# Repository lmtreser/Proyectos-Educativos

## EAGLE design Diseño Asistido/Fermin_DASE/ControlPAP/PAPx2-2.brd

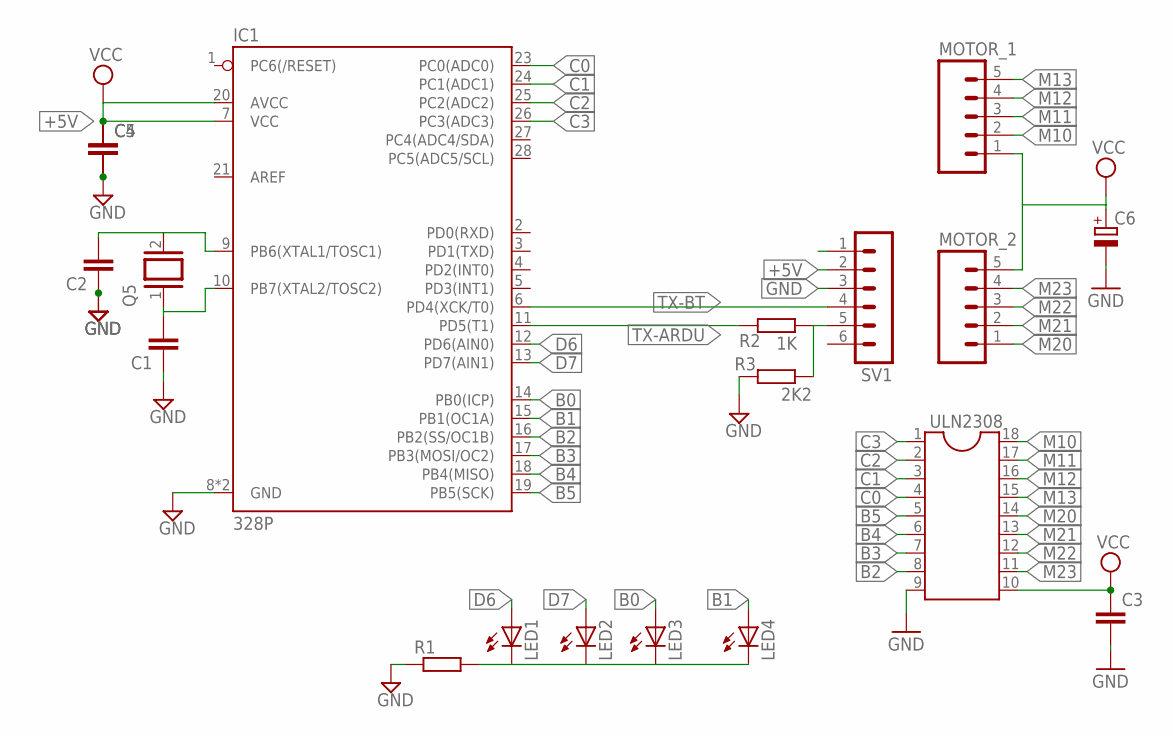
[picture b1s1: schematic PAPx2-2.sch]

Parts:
C1, C2: C-EU025-025X050; C025-025X050
C3, C4, C5: C-EU050-025X075; C050-025X075
C6: CPOL-EUE2.5-5; E2,5-5
IC1: 328P; DIP28
LED1, LED2, LED3, LED4: LED3MM; LED_3MM
MOTOR_1, MOTOR_2: M05; 05P
Q5: XTAL/S; QS
R1: R-EU_0207/7; 0207/7
R2: 1K; 0207/7
R3: 2K2; 0207/7
SV1: MA06-1
ULN2308: DIL18

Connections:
+5V: C4.1, C5.1, IC1.7 (VCC), IC1.20 (AVCC), SV1.2
B0: IC1.14 (PB0(ICP)), LED3.A
B1: IC1.15 (PB1(OC1A)), LED4.A
B2: IC1.16 (PB2(SS/OC1B)), ULN2308.8
B3: IC1.17 (PB3(MOSI/OC2)), ULN2308.7
B4: IC1.18 (PB4(MISO)), ULN2308.6
B5: IC1.19 (PB5(SCK)), ULN2308.5
C0: IC1.23 (PC0(ADC0)), ULN2308.4
C1: IC1.24 (PC1(ADC1)), ULN2308.3
C2: IC1.25 (PC2(ADC2)), ULN2308.2
C3: IC1.26 (PC3(ADC3)), ULN2308.1
D6: IC1.12 (PD6(AIN0)), LED1.A
D7: IC1.13 (PD7(AIN1)), LED2.A
GND: C1.1, C2.1, C3.2, C4.2, C5.2, C6.-, IC1.8 (GND), IC1.22 (GND), R1.1, R3.1, SV1.3, ULN2308.9
M10: MOTOR_1.2, ULN2308.18
M11: MOTOR_1.3, ULN2308.17
M12: MOTOR_1.4, ULN2308.16
M13: MOTOR_1.5, ULN2308.15
M20: MOTOR_2.1, ULN2308.14
M21: MOTOR_2.2, ULN2308.13
M22: MOTOR_2.3, ULN2308.12
M23: MOTOR_2.4, ULN2308.11
unnamed: R2.2, R3.2, SV1.5
unnamed: C1.2, IC1.10 (PB7(XTAL2/TOSC2)), Q5.1
unnamed: C2.2, IC1.9 (PB6(XTAL1/TOSC1)), Q5.2
unnamed: LED1.K (C), LED2.K (C), LED3.K (C), LED4.K (C), R1.2
TX-ARDU: IC1.11 (PD5(T1)), R2.1
TX-BT: IC1.6 (PD4(XCK/T0)), SV1.4
VCC: C3.1, C6.+, MOTOR_1.1, MOTOR_2.5, ULN2308.10

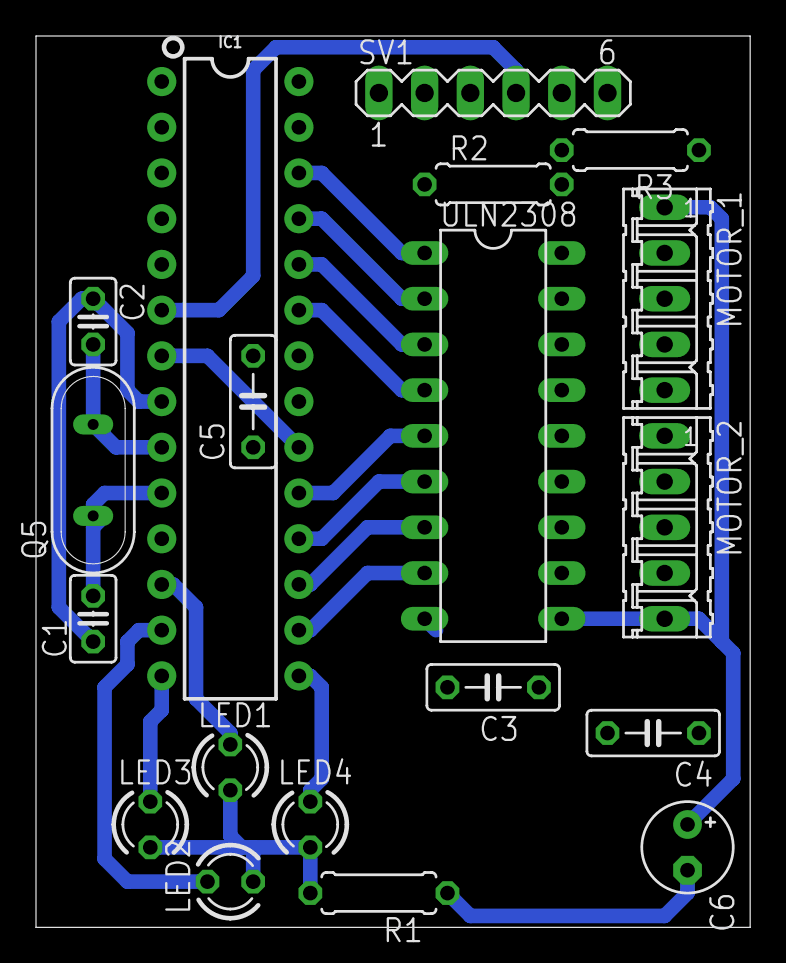
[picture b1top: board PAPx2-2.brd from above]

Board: 2 copper layers, 39.7 x 49.5 mm, 19 parts (0 on the bottom side), 29 nets.

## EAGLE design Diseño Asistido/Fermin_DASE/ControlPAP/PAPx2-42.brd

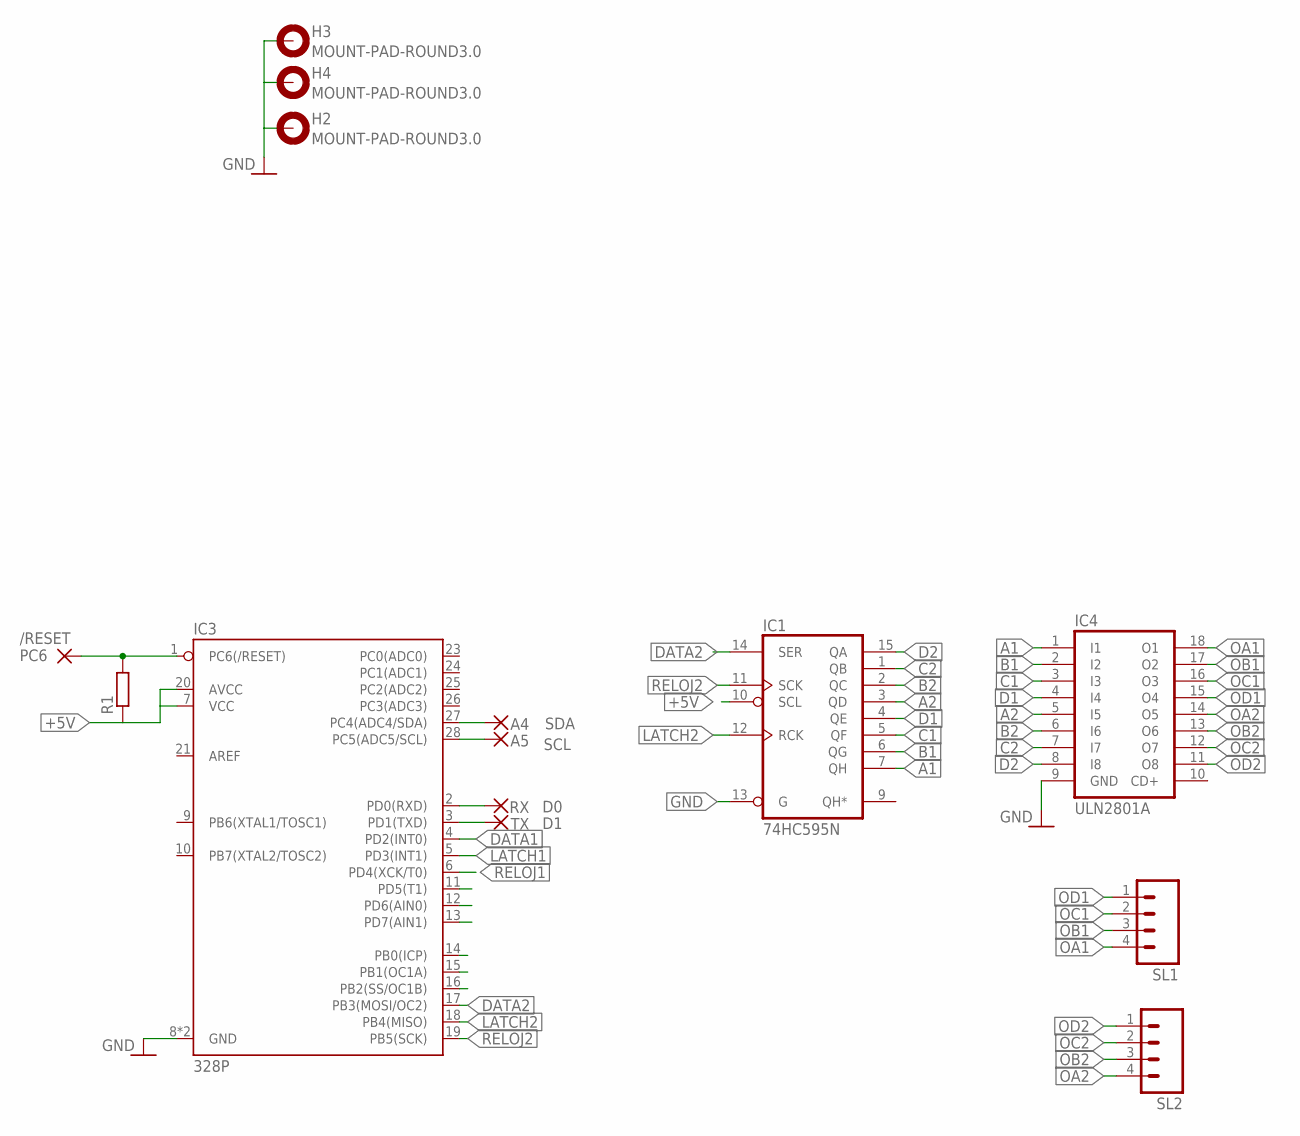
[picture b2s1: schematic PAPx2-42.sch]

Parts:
/RESET: PC6; 1,6/0,8
A4: SDA; 1,6/0,8
A5: SCL; 1,6/0,8
H2, H3, H4: MOUNT-PAD-ROUND3.0; 3,0-PAD
IC1: 74HC595N; DIL16
IC3: 328P; DIP28
IC4: ULN2801A; DIL18
R1: R-EU_0204/7; 0204/7
RX: D0; 1,6/0,8
SL1, SL2: M04; 04P
TX: D1; 1,6/0,8

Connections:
+5V: IC1.10 (SCL), IC3.7 (VCC), IC3.20 (AVCC), R1.1
A1: IC1.7 (QH), IC4.1 (I1)
A2: IC1.3 (QD), IC4.5 (I5)
B1: IC1.6 (QG), IC4.2 (I2)
B2: IC1.2 (QC), IC4.6 (I6)
C1: IC1.5 (QF), IC4.3 (I3)
C2: IC1.1 (QB), IC4.7 (I7)
D1: IC1.4 (QE), IC4.4 (I4)
D2: IC1.15 (QA), IC4.8 (I8)
DATA1: IC3.4 (PD2(INT0))
DATA2: IC1.14 (SER), IC3.17 (PB3(MOSI/OC2))
GND: H2.B3,0, H3.B3,0, H4.B3,0, IC1.8 (GND), IC1.13 (G), IC3.8 (GND), IC3.22 (GND), IC4.9 (GND)
LATCH1: IC3.5 (PD3(INT1))
LATCH2: IC1.12 (RCK), IC3.18 (PB4(MISO))
unnamed: IC3.2 (PD0(RXD)), RX.1
unnamed: IC3.3 (PD1(TXD)), TX.1
unnamed: /RESET.1, IC3.1 (PC6(/RESET)), R1.2
unnamed: A4.1, IC3.27 (PC4(ADC4/SDA))
unnamed: A5.1, IC3.28 (PC5(ADC5/SCL))
OA1: IC4.18 (O1), SL1.4
OA2: IC4.14 (O5), SL2.4
OB1: IC4.17 (O2), SL1.3
OB2: IC4.13 (O6), SL2.3
OC1: IC4.16 (O3), SL1.2
OC2: IC4.12 (O7), SL2.2
OD1: IC4.15 (O4), SL1.1
OD2: IC4.11 (O8), SL2.1
RELOJ1: IC3.6 (PD4(XCK/T0))
RELOJ2: IC1.11 (SCK), IC3.19 (PB5(SCK))
VCC: IC1.16 (VCC)

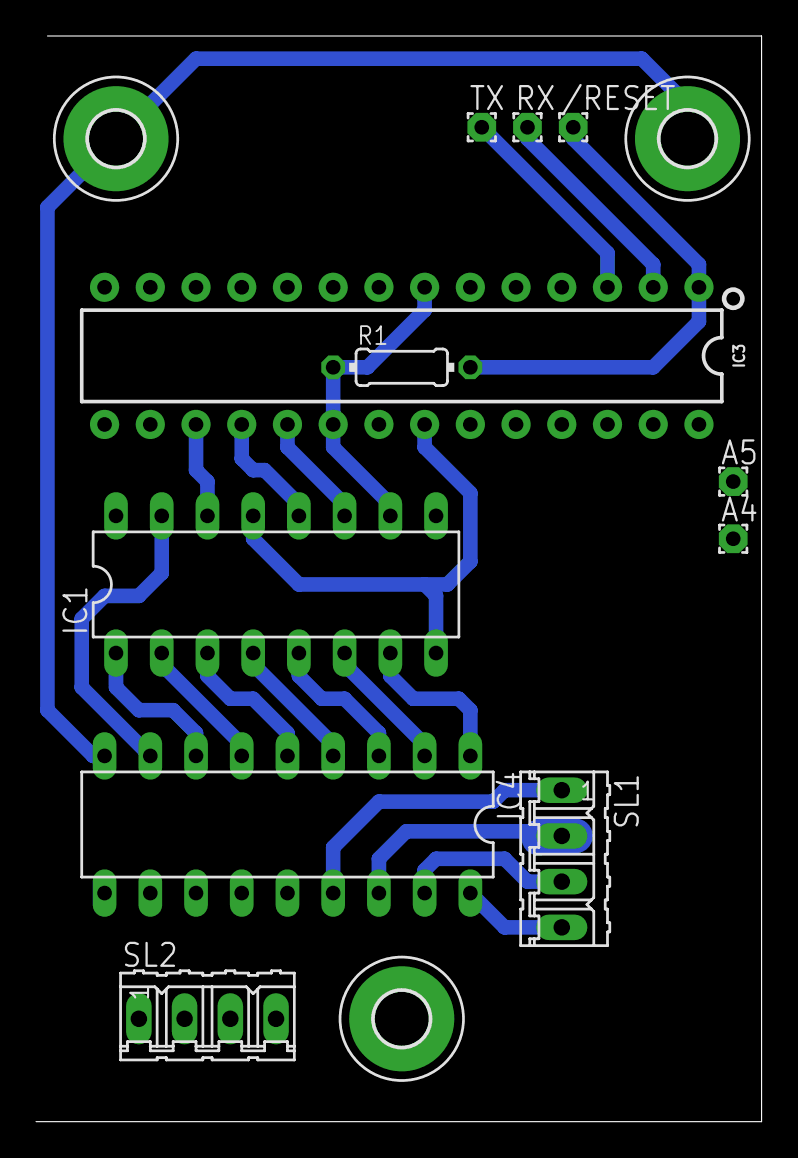
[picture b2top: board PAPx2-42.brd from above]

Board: 2 copper layers, 40.3 x 60.3 mm, 14 parts (0 on the bottom side), 26 nets.

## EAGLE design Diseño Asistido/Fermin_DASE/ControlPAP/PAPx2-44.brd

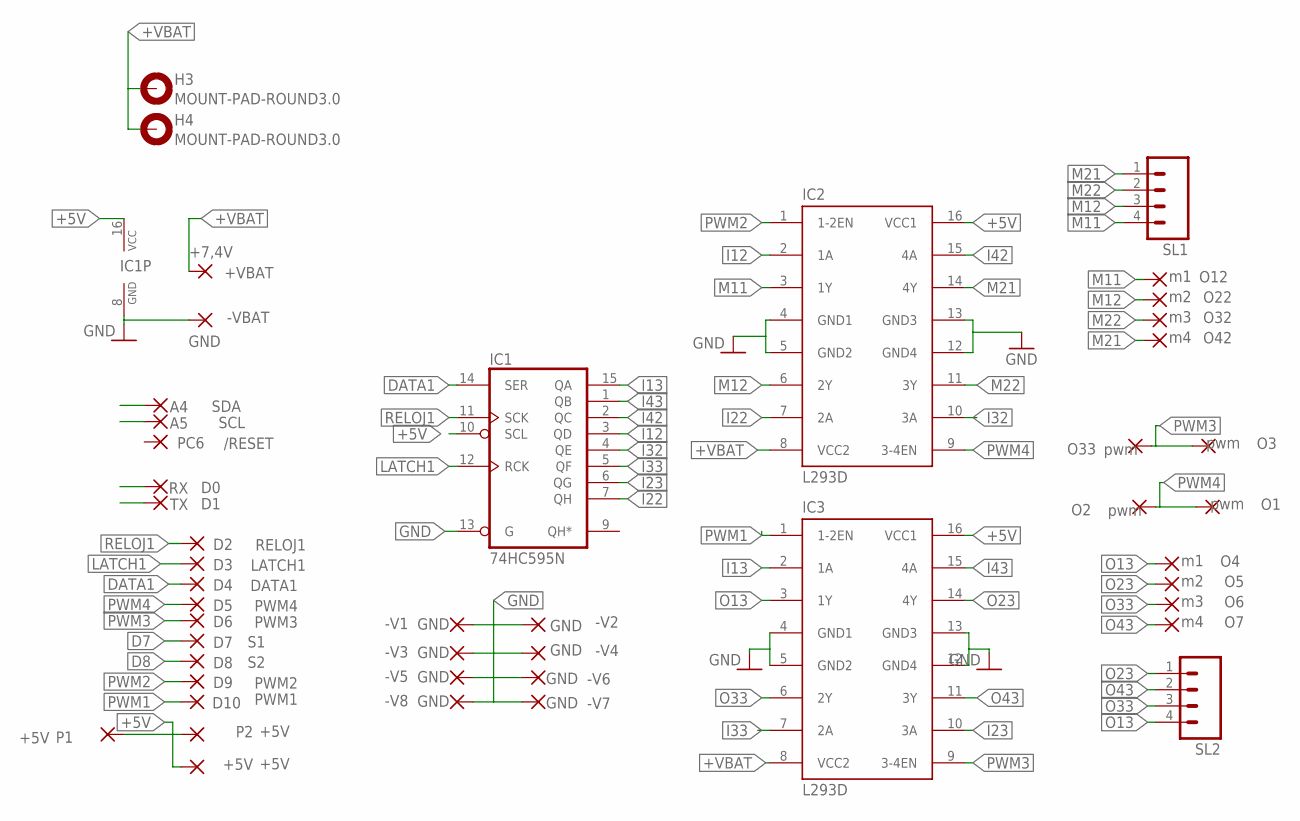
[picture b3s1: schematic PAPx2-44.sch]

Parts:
+5V: +5V; 1,6/0,8
+VBAT: +7,4V; 1,6/0,8
-V1, -V2, -V3, -V4, -V5, -V6, -V7, -V8: GND; 1,6/0,8
-VBAT: GND; 1,6/0,8
/RESET: PC6; 1,6/0,8
A4: SDA; 1,6/0,8
A5: SCL; 1,6/0,8
D7: S1; 1,6/0,8
D8: S2; 1,6/0,8
DATA1: D4; 1,6/0,8
H3, H4: MOUNT-PAD-ROUND3.0; 3,0-PAD
IC1: 74HC595N; DIL16
IC2, IC3: L293D; DIL16
LATCH1: D3; 1,6/0,8
O1, O2, O3, O33: pwm; 1,6/0,8
O4, O12: m1; 1,6/0,8
O5, O22: m2; 1,6/0,8
O6, O32: m3; 1,6/0,8
O7, O42: m4; 1,6/0,8
P1, P2: +5V; 1,6/0,8
PWM1: D10; 1,6/0,8
PWM2: D9; 1,6/0,8
PWM3: D6; 1,6/0,8
PWM4: D5; 1,6/0,8
RELOJ1: D2; 1,6/0,8
RX: D0; 1,6/0,8
SL1, SL2: M04; 04P
TX: D1; 1,6/0,8

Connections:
+5V: +5V.1, IC1.10 (SCL), IC1.16 (VCC), IC2.16 (VCC1), IC3.16 (VCC1), P1.1, P2.1
+VBAT: +VBAT.1, H3.B3,0, H4.B3,0, IC2.8 (VCC2), IC3.8 (VCC2)
D7: D7.1
D8: D8.1
DATA1: DATA1.1, IC1.14 (SER)
GND: -V1.1, -V2.1, -V3.1, -V4.1, -V5.1, -V6.1, -V7.1, -V8.1, -VBAT.1, IC1.8 (GND), IC1.13 (G), IC2.4 (GND1), IC2.5 (GND2), IC2.12 (GND4), IC2.13 (GND3), IC3.12 (GND4), IC3.13 (GND3)
I12: IC1.3 (QD), IC2.2 (1A)
I13: IC1.15 (QA), IC3.2 (1A)
I22: IC1.7 (QH), IC2.7 (2A)
I23: IC1.6 (QG), IC3.10 (3A)
I32: IC1.4 (QE), IC2.10 (3A)
I33: IC1.5 (QF), IC3.7 (2A)
I42: IC1.2 (QC), IC2.15 (4A)
I43: IC1.1 (QB), IC3.15 (4A)
LATCH1: IC1.12 (RCK), LATCH1.1
M11: IC2.3 (1Y), O12.1, SL1.4
M12: IC2.6 (2Y), O22.1, SL1.3
M21: IC2.14 (4Y), O42.1, SL1.1
M22: IC2.11 (3Y), O32.1, SL1.2
unnamed: IC3.4 (GND1), IC3.5 (GND2)
O13: IC3.3 (1Y), O4.1, SL2.4
O23: IC3.14 (4Y), O5.1, SL2.1
O33: IC3.6 (2Y), O6.1, SL2.3
O43: IC3.11 (3Y), O7.1, SL2.2
PWM1: IC3.1 (1-2EN), PWM1.1
PWM2: IC2.1 (1-2EN), PWM2.1
PWM3: IC3.9 (3-4EN), O3.1, O33.1, PWM3.1
PWM4: IC2.9 (3-4EN), O1.1, O2.1, PWM4.1
RELOJ1: IC1.11 (SCK), RELOJ1.1

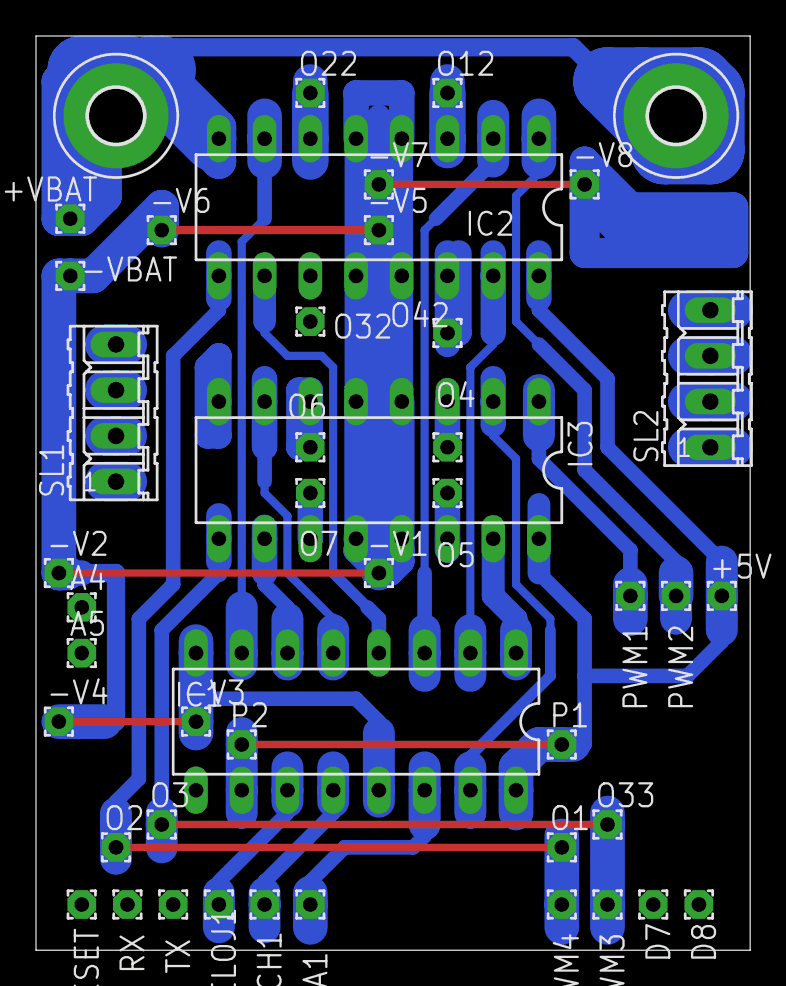
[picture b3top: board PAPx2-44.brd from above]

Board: 2 copper layers, 39.7 x 50.8 mm, 46 parts (0 on the bottom side), 27 nets.

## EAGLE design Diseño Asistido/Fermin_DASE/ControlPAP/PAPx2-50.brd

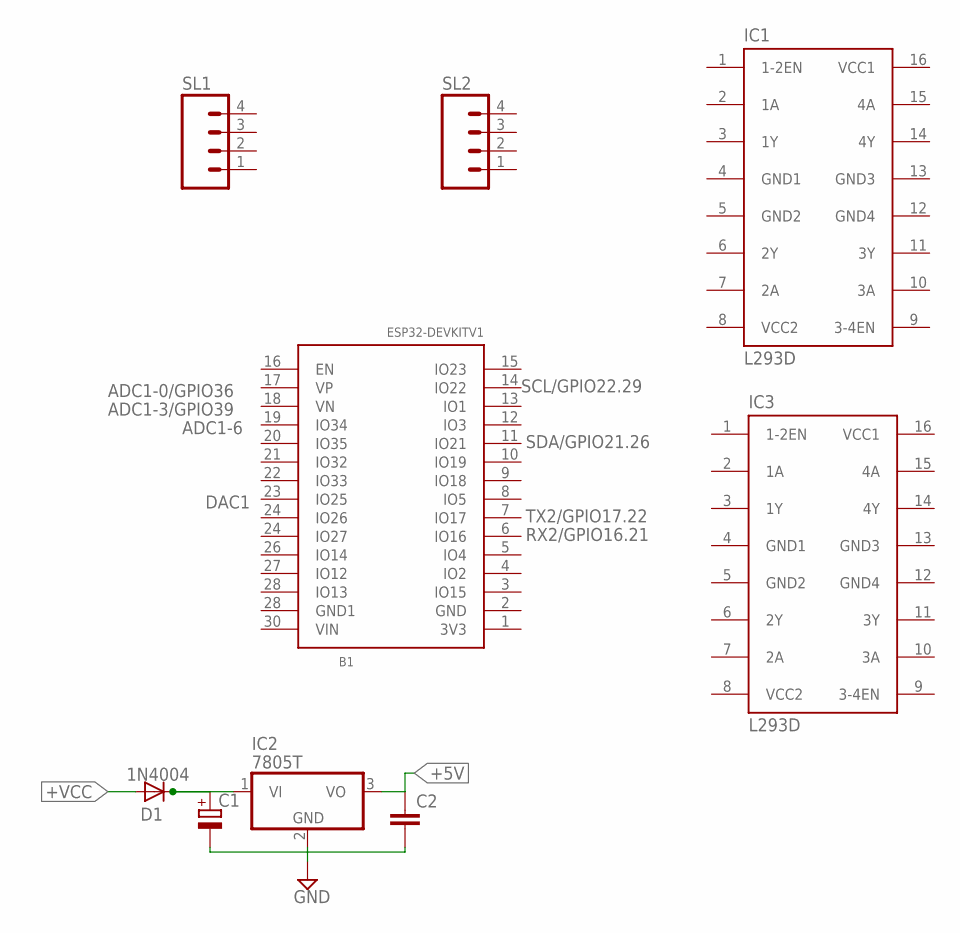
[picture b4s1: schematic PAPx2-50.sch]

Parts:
B1: ESP32_DEV_KIT_V1; ESP32-DEVKITV1
C1: CPOL-EUE2.5-6; E2,5-6
C2: C-EU025-025X050; C025-025X050
D1: 1N4004; DO41-10
IC1, IC3: L293D; DIL16
IC2: 7805T; TO220H
SL1, SL2: M04; 04P

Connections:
+5V: C2.1, IC2.3 (VO)
+VCC: D1.A
GND: C1.-, C2.2, IC2.2 (GND)
GND1: IC1.4 (GND1), IC3.4 (GND1)
GND2: IC1.5 (GND2), IC3.5 (GND2)
GND3: IC1.13 (GND3), IC3.13 (GND3)
GND4: IC1.12 (GND4), IC3.12 (GND4)
unnamed: C1.+, D1.C, IC2.1 (VI)
VCC1: IC1.16 (VCC1), IC3.16 (VCC1)
VCC2: IC1.8 (VCC2), IC3.8 (VCC2)

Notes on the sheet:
ADC1-0/GPIO36
ADC1-3/GPIO39
DAC1
SCL/GPIO22.29
SDA/GPIO21.26
TX2/GPIO17.22
RX2/GPIO16.21
ADC1-6

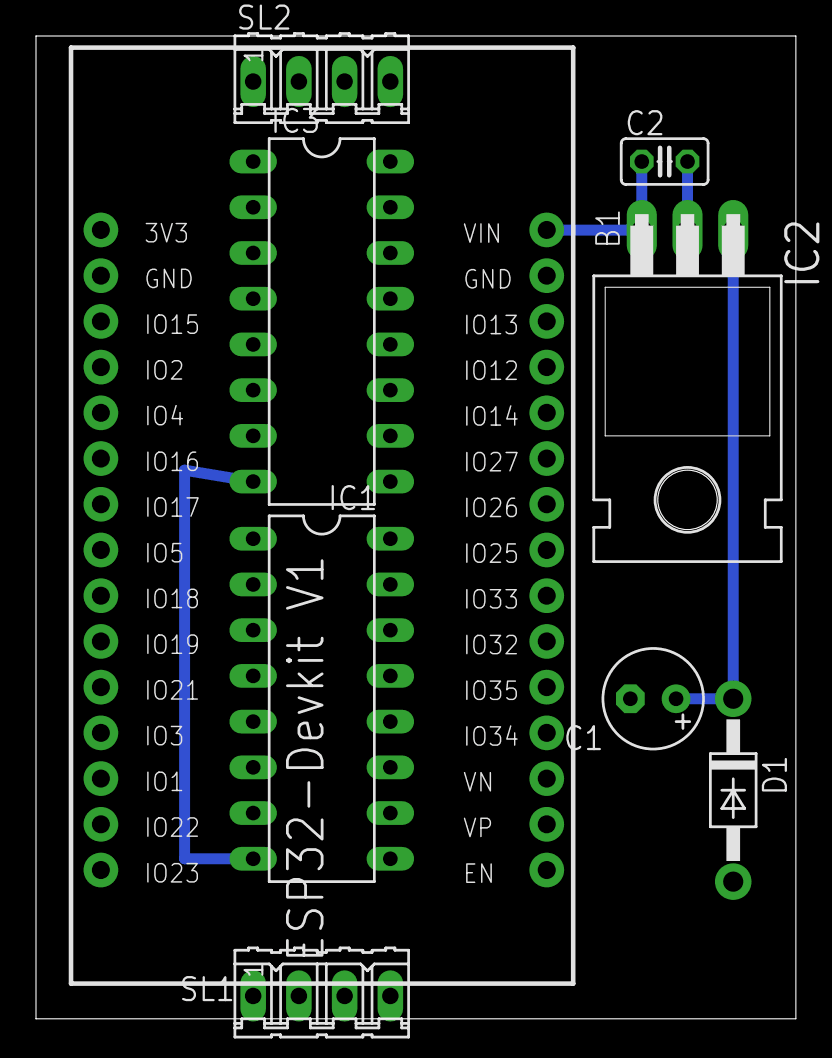
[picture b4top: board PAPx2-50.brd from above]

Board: 2 copper layers, 42.2 x 54.6 mm, 9 parts (0 on the bottom side), 9 nets.

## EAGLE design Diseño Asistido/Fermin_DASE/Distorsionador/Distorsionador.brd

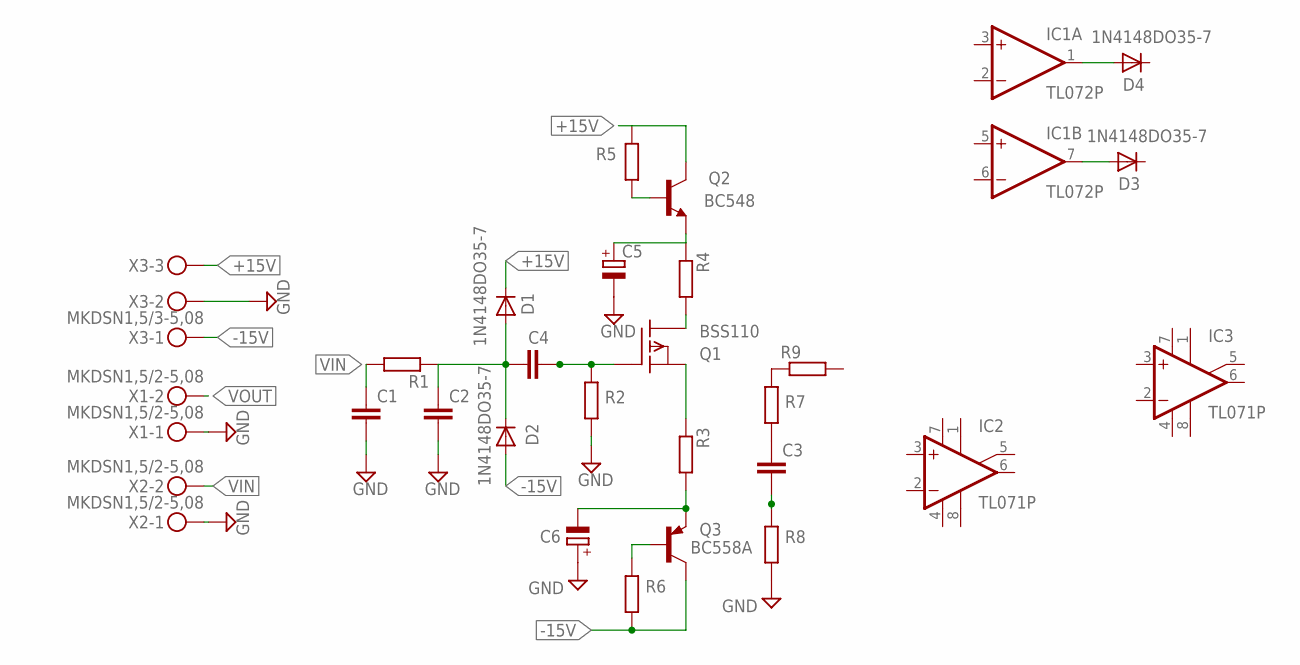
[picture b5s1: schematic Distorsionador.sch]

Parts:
C1, C2, C3, C4: C-EU025-025X050; C025-025X050
C5, C6: CPOL-EUE2.5-5; E2,5-5
D1, D2, D3, D4: 1N4148DO35-7; DO35-7
IC1: TL072P; DIL08
IC2, IC3: TL071P; DIL08
Q1: BSS110; TO92
Q2: BC548; TO92-EBC
Q3: BC558A; TO92-EBC
R1, R2, R3, R4, R5, R6, R7, R8, R9: R-EU_0207/7; 0207/7
X1, X2: MKDSN1,5/2-5,08
X3: MKDSN1,5/3-5,08

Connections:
+15V: D1.C, Q2.C, R5.1, X3.3
-15V: D2.A, Q3.C, R6.2, X3.1
GND: C1.2, C2.2, C5.-, C6.+, R2.2, R8.2, X1.1, X2.1, X3.2
unnamed: C4.2, Q1.2 (G), R2.1
unnamed: C5.+, Q2.E, R4.1
unnamed: Q2.B, R5.2
unnamed: C6.-, Q3.E, R3.2
unnamed: R7.1, R9.1
unnamed: Q3.B, R6.1
unnamed: C3.1, R7.2
unnamed: Q1.1 (S), R3.1
unnamed: Q1.3 (D), R4.2
unnamed: C2.1, C4.1, D1.A, D2.C, R1.1
unnamed: C3.2, R8.1
unnamed: D3.A, IC1.7 (OUT)
unnamed: D4.A, IC1.1 (OUT)
V+: IC1.8 (V+), IC2.7 (V+), IC3.7 (V+)
V-: IC1.4 (V-), IC2.4 (V-), IC3.4 (V-)
VIN: C1.1, R1.2, X2.2
VOUT: X1.2

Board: 2 copper layers, 28 parts (0 on the bottom side), 19 nets, no tracks yet.
